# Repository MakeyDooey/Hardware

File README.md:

# Hardware
This includes all CAD files, PCB designs, schematics, datasheets, and designs. (includes enclosure and modularity components)

In it's current state I do not have a .gitignore for this repo. I will make one eventually and organize the repo more, but for now all KiCAD files are saved in the Schematic Folder as they are saved on my local computer

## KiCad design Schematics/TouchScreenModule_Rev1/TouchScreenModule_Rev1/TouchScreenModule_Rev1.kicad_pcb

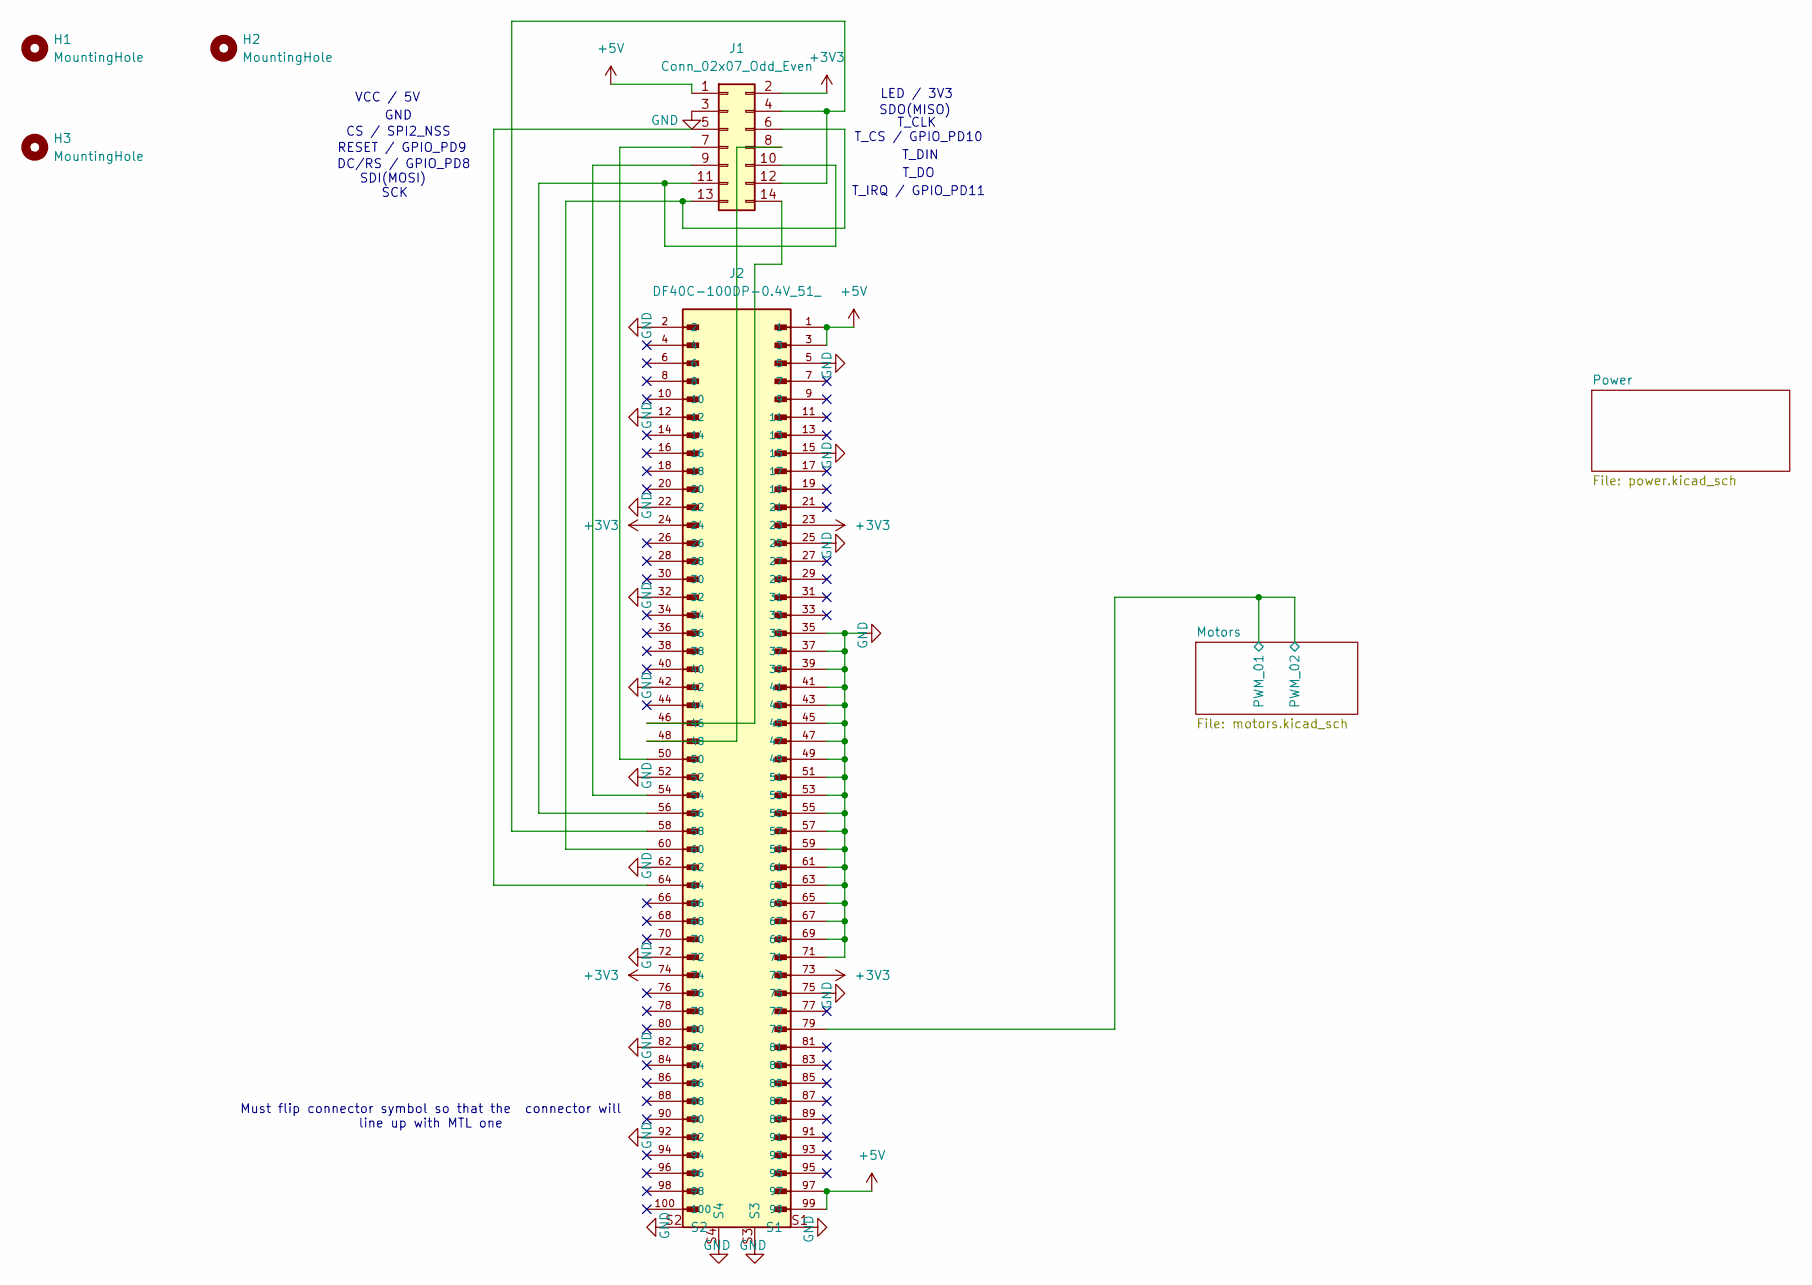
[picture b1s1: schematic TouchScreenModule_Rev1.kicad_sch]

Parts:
H1, H2, H3: MountingHole; MountingHole_3.2mm_M3_Pad_TopOnly
J1: Conn_02x07_Odd_Even; PinHeader_2x07_P2.54mm_Vertical
J2: DF40C-100DP-0.4V_51_; HIROSE_DF40C-100DP-0.4V_51_; PARTREV 8

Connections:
+3V3: J1.2, J2.23, J2.24, J2.73, J2.74
+5V: J1.1, J2.1, J2.3, J2.97, J2.99; also elsewhere on the board
/Motors/PWM_01: J2.79; also elsewhere on the board
GND: J1.3, J2.2, J2.5, J2.12, J2.15, J2.22, J2.25, J2.32, J2.35, J2.37, J2.39, J2.41, J2.42, J2.43, J2.45, J2.47, J2.49, J2.51, J2.52, J2.53, J2.55, J2.57, J2.59, J2.61, J2.62, J2.63, J2.65, J2.67, J2.69, J2.71, J2.72, J2.75, J2.82, J2.92, J2.S1, J2.S2, J2.S3, J2.S4; also elsewhere on the board
unnamed: J1.5, J2.64
unnamed: J1.7, J2.50
unnamed: J1.8, J2.48
unnamed: J1.9, J2.54
unnamed: J1.10, J1.11, J2.56
unnamed: J1.4, J1.12, J2.58
unnamed: J1.6, J1.13, J2.60
unnamed: J1.14, J2.46

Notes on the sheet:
T_CLK
CS / SPI2_NSS
GND
SCK
T_IRQ / GPIO_PD11
T_CS / GPIO_PD10
SDI(MOSI)
RESET / GPIO_PD9
T_DIN
T_DO
VCC / 5V
DC/RS / GPIO_PD8
SDO(MISO)
Must flip connector symbol so that the connector will line up with MTL one
LED / 3V3

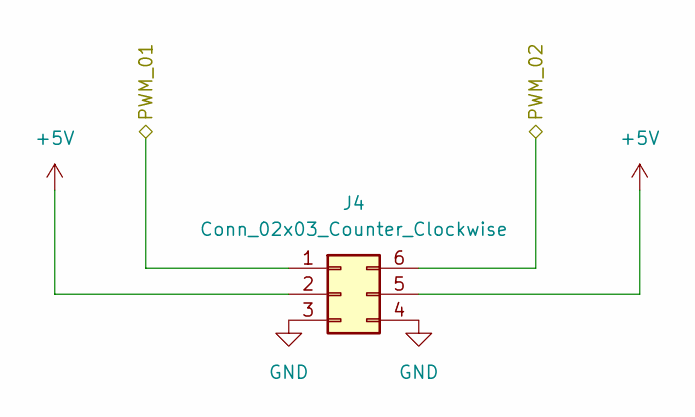
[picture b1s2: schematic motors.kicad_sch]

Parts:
J4: Conn_02x03_Counter_Clockwise; PinHeader_2x03_P2.54mm_Vertical

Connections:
+5V: J4.2, J4.5; also elsewhere on the board
/Motors/PWM_01: J4.1, J4.6; also elsewhere on the board
GND: J4.3, J4.4; also elsewhere on the board

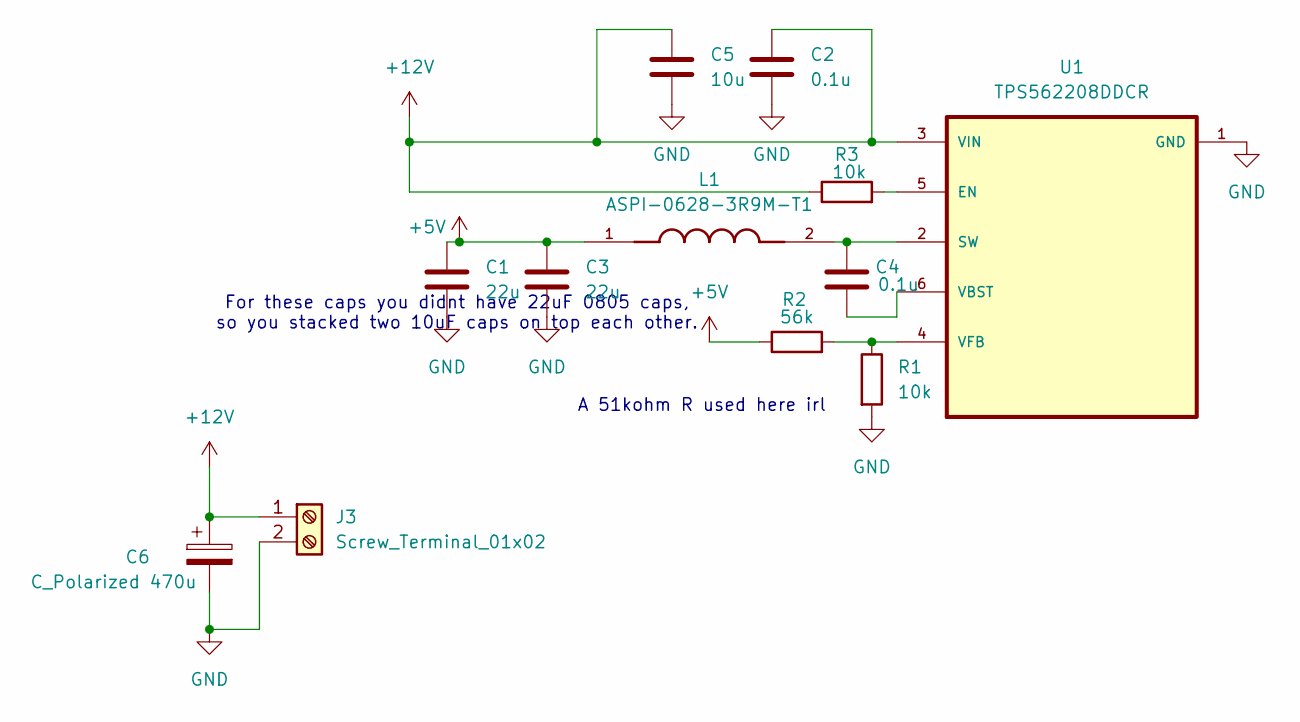
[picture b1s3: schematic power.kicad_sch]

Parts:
C1, C3: 22u; C_0805_2012Metric_Pad1.18x1.45mm_HandSolder
C2, C4: 0.1u; C_0805_2012Metric_Pad1.18x1.45mm_HandSolder
C5: 10u; C_0805_2012Metric_Pad1.18x1.45mm_HandSolder
C6: C_Polarized 470u; CP_Radial_D6.3mm_P2.50mm
J3: Screw_Terminal_01x02; TerminalBlock_Phoenix_MKDS-1,5-2-5.08_1x02_P5.08mm_Horizont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
L1: ASPI-0628-3R9M-T1; IND_ASPI-0628-3R9M-T1; PARTREV 6/30/2022
R1, R3: 10k; R_0805_2012Metric_Pad1.20x1.40mm_HandSolder
R2: 56k; R_0805_2012Metric_Pad1.20x1.40mm_HandSolder
U1: TPS562208DDCR

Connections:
+5V: C1.1, C3.1, L1.1, R2.1; also elsewhere on the board
+12V: C2.1, C5.1, C6.1, J3.1, R3.1, U1.3 (VIN)
GND: C1.2, C2.2, C3.2, C5.2, C6.2, J3.2, R1.2, U1.1 (GND); also elsewhere on the board
unnamed: R3.2, U1.5 (EN)
unnamed: C4.2, L1.2, U1.2 (SW)
unnamed: C4.1, U1.6 (VBST)
unnamed: R1.1, R2.2, U1.4 (VFB)

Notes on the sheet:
For these caps you didnt have 22uF 0805 caps, so you stacked two 10uF caps on top each other.
A 51kohm R used here irl

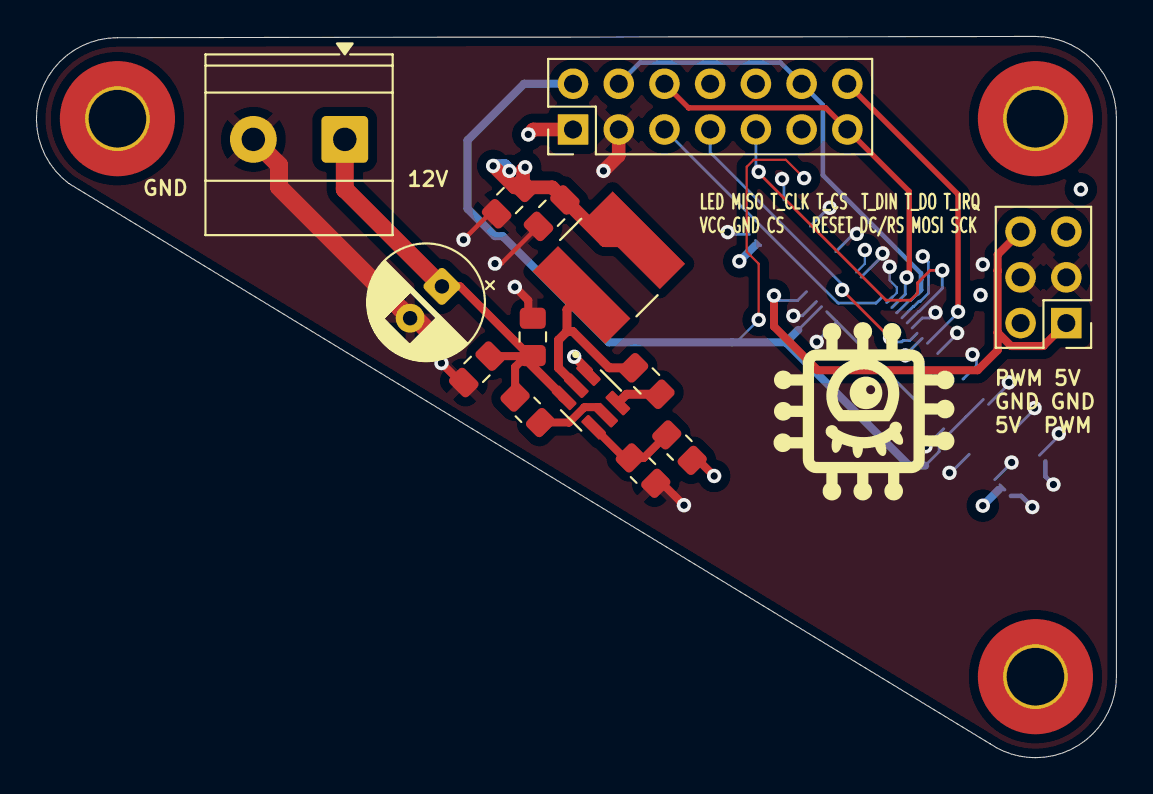
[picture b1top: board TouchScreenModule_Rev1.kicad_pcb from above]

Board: 4 copper layers, 60.0 x 40.1 mm, 18 parts (1 on the bottom side), 17 nets.

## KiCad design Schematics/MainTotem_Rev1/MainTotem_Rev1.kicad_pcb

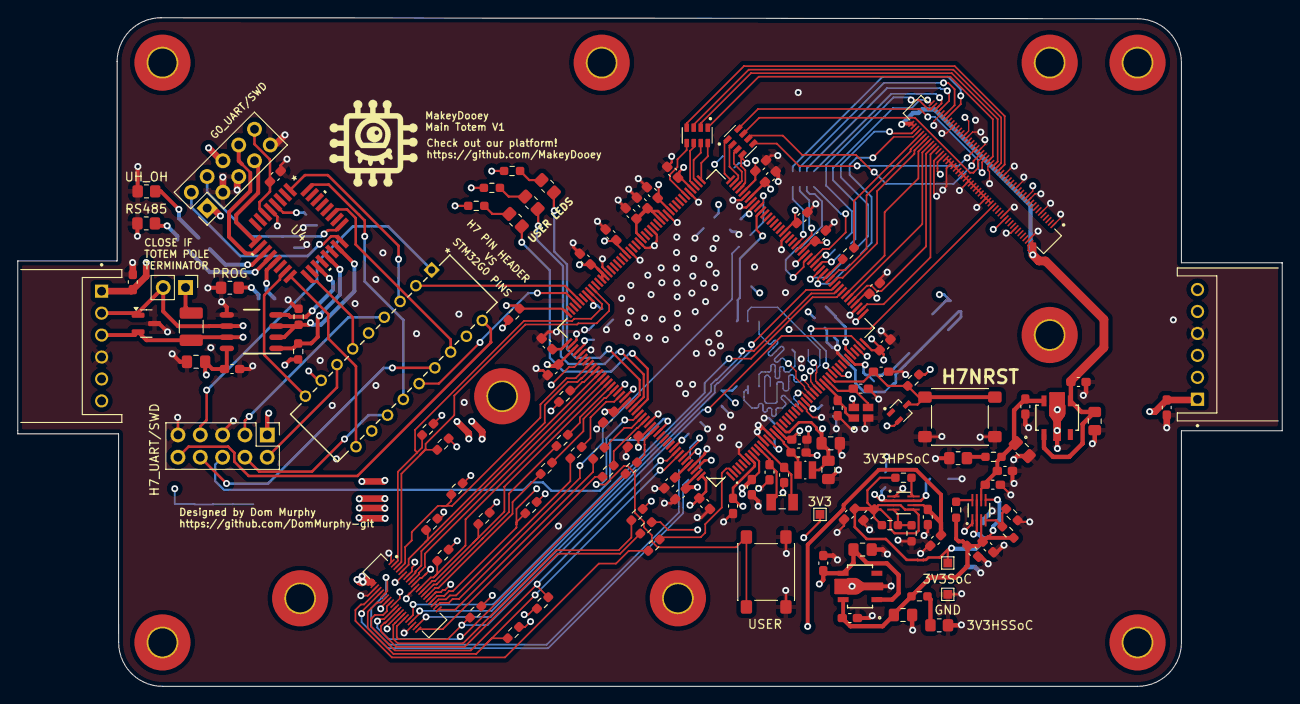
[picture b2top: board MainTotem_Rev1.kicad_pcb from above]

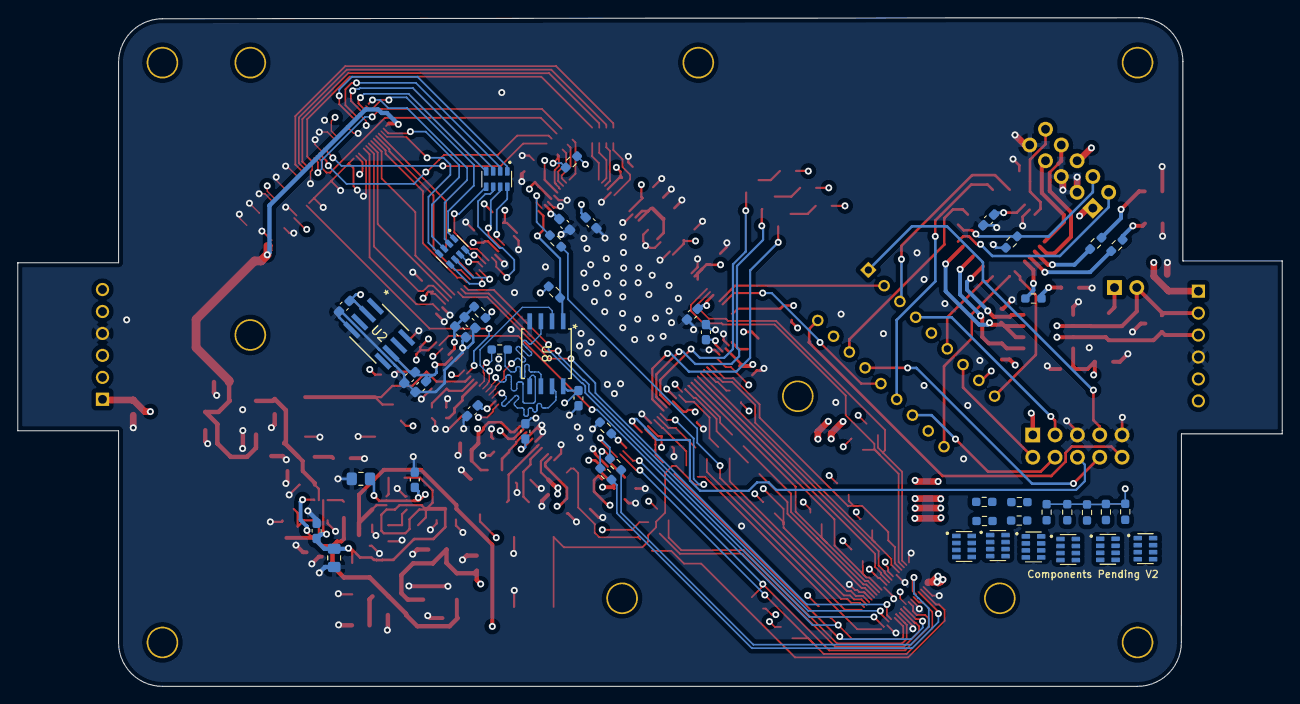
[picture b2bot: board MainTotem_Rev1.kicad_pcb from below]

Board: 4 copper layers, 143.9 x 76.1 mm, 181 parts (48 on the bottom side), 159 nets.

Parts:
3V3, 3V3SoC: TestPoint; TestPoint_Pad_1.0x1.0mm
3V3HPSoC: YELLOW; R_0805_2012Metric_Pad1.20x1.40mm_HandSolder
3V3HSSoC: GREEN; R_0805_2012Metric_Pad1.20x1.40mm_HandSolder
C1, C2, C3, C4, C5, C6, C7, C8, C9, C10, C11, C12, C13, C14, C15, C16, C19, C21, C22, C26, C27, C32, C34, C35, C38, C39, C47, C48, C49, C51, C52, C54, C63: 100n; C_0603_1608Metric_Pad1.08x0.95mm_HandSolder
C17, C41, C43, C72, C74: 4.7u; C_0603_1608Metric_Pad1.08x0.95mm_HandSolder
C18, C20: 1u; C_0603_1608Metric_Pad1.08x0.95mm_HandSolder
C23, C25, C42, C44, C45, C64, C73, C75, C76: 0.1u; C_0603_1608Metric_Pad1.08x0.95mm_HandSolder
C24, C33, C36, C37, C40: 10u; C_0805_2012Metric_Pad1.18x1.45mm_HandSolder
C28, C29, C30, C31: 2.2u ESR<100m; C_0603_1608Metric_Pad1.08x0.95mm_HandSolder
C46, C77: 22u; C_0805_2012Metric_Pad1.18x1.45mm_HandSolder
C55: 4.7u ESR<100m; C_0603_1608Metric_Pad1.08x0.95mm_HandSolder
C56: 220pF; C_0603_1608Metric_Pad1.08x0.95mm_HandSolder
C57, C58: 10u ESR<20m; C_0805_2012Metric_Pad1.18x1.45mm_HandSolder
C59, C60: 12p; C_0603_1608Metric_Pad1.08x0.95mm_HandSolder
C61, C62: 15p; C_0603_1608Metric_Pad1.08x0.95mm_HandSolder
D1: SM712_SOT23; SOT-23
D2: GREEN; R_0805_2012Metric_Pad1.20x1.40mm_HandSolder
D3: YELLOW; R_0805_2012Metric_Pad1.20x1.40mm_HandSolder
D4: BAT54SW_115
D6: RED; R_0805_2012Metric_Pad1.20x1.40mm_HandSolder
FB1: MFBW1V1608-601-R; R_0603_1608Metric_Pad0.98x0.95mm_HandSolder
GND: TestPoint; TestPoint_Pad_1.0x1.0mm
H1, H2, H3, H4, H5, H7, H8, H9, H10, H11: MountingHole; MountingHole_3.2mm_M3_Pad_TopOnly
H7RST1: SW_Push; SW_SPST_PTS645Sx43SMTR92
H7_UART/SWD: Conn_02x05_Odd_Even; PinHeader_2x05_P2.54mm_Vertical
J1, J2: S6B-XH-A; JST_S6B-XH-A
J3: Conn_02x05_Odd_Even; PinHeader_2x05_P2.54mm_Vertical
J5: DF40C-100DS-0.4V_51_; HIROSE_DF40C-100DS-0.4V_51_
J6: DF40C-40DS-0.4V_51_; HIROSE_DF40C-40DS-0.4V_51_
JP1: Jumper_2_Open; PinHeader_1x02_P2.54mm_Vertical
L1: VLS252012CX-2R2M-1; IND_VLS252012CX-2R2M-1
MainClock1: ABM10W-24.0000MHZ-8-D1X-T3; XTAL_ABM10W-24.0000MHZ-8-D1X-T3
PROG: GREEN; R_0805_2012Metric_Pad1.20x1.40mm_HandSolder
R1: 120; R_1210_3225Metric_Pad1.30x2.65mm_HandSolder
R2, R3, R4, R5, R6, R7, R16, R25, R26, R27, R28, R29, R31, R32, R48, R49, R52, R53: 10k; R_0603_1608Metric_Pad0.98x0.95mm_HandSolder
R8, R9, R10, R11, R12, R17, R18, R22: 1k; R_0603_1608Metric_Pad0.98x0.95mm_HandSolder
R13, R20: 56k; R_0603_1608Metric_Pad0.98x0.95mm_HandSolder
R14, R19: 110k; R_0603_1608Metric_Pad0.98x0.95mm_HandSolder
R15, R21: 100k; R_0603_1608Metric_Pad0.98x0.95mm_HandSolder
R23, R24, R44, R50, R51: 4.7k; R_0603_1608Metric_Pad0.98x0.95mm_HandSolder
R30, R33, R34, R35, R36, R37, R38, R39, R40, R41, R42, R43, R45, R46, R47, R54, R55, R56, R57: 33; R_0603_1608Metric_Pad0.98x0.95mm_HandSolder
RN1, RN2, RN3, RN4, RN5, RN6, RN7, RN8, RN9, RN10: CAY16-330J4LF; 33ohmresarray
RS485: YELLOW; R_0805_2012Metric_Pad1.20x1.40mm_HandSolder
RTC1: ABS07-32.768KHZ-9-T; XTAL_ABS07-32.768KHZ-9-T
SW1: 3-1825010-8; SW6_3-1825010-8_TEC
U1: STM32H757IIT6; LQFP-176
U2: ADR4525BRZ-R7; R_8_ADI-M
U3: THVD1450D; D0008A_M
U4: STM32G071KBT6; LQFP-32-M
U5, U6: AP7361C-33Y5-13; SOT89-5_DIO-M
U7, U11: PTPS2117DRLR; SOT-5X3-8_DRL_TEX-M
U8: W25Q128JVSIQ TR; SOIC_208MIL_WIN-M
UH_OH: RED; R_0805_2012Metric_Pad1.20x1.40mm_HandSolder
USER: SW_Push; SW_SPST_PTS645Sx43SMTR92

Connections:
3V3MODULES: 3V3SoC.1, C45.1, C46.1, C72.1, C73.1, R19.1, R21.1, U7.2 (VOUT), U7.7 (VOUT), U11.3 (VIN1), U11.5 (MODE)
3V3PROGRAMMER: C23.1, C64.1, C74.1, C75.1, J1.1, J2.1, U11.6 (VIN2)
5VHPSoC: C33.1, C34.1, J5.2, J5.4, J5.98, J5.100, U5.1 (EN), U5.4 (IN)
5VHSSoC: C37.1, C38.1, J6.2, J6.4, U6.1 (EN), U6.4 (IN)
+3V3: 3V3.1, C1.1, C2.1, C3.1, C4.1, C5.1, C6.1, C7.1, C8.1, C9.1, C10.1, C11.1, C12.1, C13.1, C14.1, C15.1, C16.1, C17.1, C22.1, C24.1, C25.1, C32.1, C51.1, C54.1, C55.1, C63.1, C76.1, C77.1, FB1.2, H7_UART/SWD.1, J3.1, J3.6, J5.23, J5.24, J5.73, J5.74, J6.19, J6.20, R2.1, R5.1, R6.1, R16.2, R17.1, R18.1, R22.1, R23.1, R24.1, R25.1, R26.1, R27.1, R28.1, R29.1, R31.1, R32.1, R44.1, R48.1, R49.1, R50.1, R51.1, R52.1, R53.1, U1.7 (VDD), U1.8 (VBAT), U1.13 (VDD), U1.16 (VDDSMPS), U1.25 (VDD), U1.44 (VDD), U1.48 (VDD), U1.65 (VDD), U1.71 (VDD), U1.84 (VDD), U1.92 (VDD), U1.99 (VDD), U1.113 (VDD), U1.120 (VDD50USB), U1.121 (VDD33USB), U1.126 (VDD), U1.136 (VDD), U1.152 (VDD), U1.160 (VDD), U1.174 (PDR_ON), U1.176 (VDD), U2.2 (VIN), U3.8 (VCC), U4.4 (VDD), U8.8 (VCC), U11.2 (VOUT), U11.7 (VOUT)
/MCU2/40P_CONN/FDCAN_RX: J6.15, U1.143 (PD0)
/MCU2/40P_CONN/FDCAN_TX: J6.17, U1.144 (PD1)
/MCU2/40P_CONN/GPIO_PD7: R35.1, U1.150 (PD7)
/MCU2/40P_CONN/GPIO_PE0: R42.1, U1.170 (PE0)
/MCU2/40P_CONN/GPIO_PE1: R43.1, U1.171 (PE1)
/MCU2/40P_CONN/GPIO_PE3: R45.1, U1.2 (PE3)
/MCU2/40P_CONN/I2C1_SCL: J6.18, R23.2, U1.168 (PB8)
/MCU2/40P_CONN/I2C1_SDA: J6.14, R24.2, U1.169 (PB9)
/MCU2/40P_CONN/SDMMC1_CK: R30.1, U1.142 (PC12)
/MCU2/40P_CONN/SDMMC1_CMP: J6.23, R25.2, U1.145 (PD2)
/MCU2/40P_CONN/SDMMC1_D0: J6.5, R28.2, U1.124 (PC8)
/MCU2/40P_CONN/SDMMC1_D1: J6.3, R29.2, U1.125 (PC9)
/MCU2/40P_CONN/SDMMC1_D2: J6.7, R27.2, U1.140 (PC10)
/MCU2/40P_CONN/SDMMC1_D3: J6.9, R26.2, U1.141 (PC11)
/MCU2/40P_CONN/USART2_CTS: J6.25, R32.2, U1.146 (PD3)
/MCU2/40P_CONN/USART2_RTS: R33.1, U1.147 (PD4)
/MCU2/40P_CONN/USART2_RX: J6.33, R31.2, U1.149 (PD6)
/MCU2/40P_CONN/USART2_TX: R34.1, U1.148 (PD5)
/MCU2/100P_CONN/ADC_PA3: J5.80, U1.46 (PA3)
/MCU2/100P_CONN/ADC_PA6: J5.86, U1.51 (PA6)
/MCU2/100P_CONN/ADC_PB0: J5.88, U1.55 (PB0)
/MCU2/100P_CONN/ADC_PB1: J5.90, U1.56 (PB1)
/MCU2/100P_CONN/ADC_PC0: J5.34, U1.34 (PC0)
/MCU2/100P_CONN/DAC_ADC_PA4: J5.82, U1.49 (PA4)
/MCU2/100P_CONN/DAC_ADC_PA5: J5.84, U1.50 (PA5)
/MCU2/100P_CONN/GPIO_PB2: R54.1, U1.57 (PB2)
/MCU2/100P_CONN/GPIO_PE7: RN7.8, U1.67 (PE7)
/MCU2/100P_CONN/GPIO_PG0: RN7.6, U1.63 (PG0)
/MCU2/100P_CONN/GPIO_PG1: RN7.7, U1.66 (PG1)
/MCU2/QSPIMEM/QUADSPI_BK1_CLK: R57.1, U1.30 (PF10)
/MCU2/QSPIMEM/QUADSPI_BK1_IO0: U1.28 (PF8), U8.5 (DI(IO0))
/MCU2/QSPIMEM/QUADSPI_BK1_IO1: U1.29 (PF9), U8.2 (DO(IO1))
/MCU2/QSPIMEM/QUADSPI_BK1_IO2: U1.27 (PF7), U8.3 (/WP(IO2))
/MCU2/QSPIMEM/QUADSPI_BK1_IO3: U1.26 (PF6), U8.7 (/HOLD_/RESET)
BUSH7BOOT0: SW1.16, U4.27 (PB3)
BUSH7NRST: SW1.6, U4.17 (PB2)
BUSH7SWCLK: SW1.10, U4.16 (PB1)
BUSH7SWDIO: SW1.9, U4.15 (PB0)
BUSH7UARTRX: SW1.13, U4.32 (PB8)
BUSHH7UARTTX: SW1.3, U4.1 (PB9)
G0UARTRX: J3.8, U4.10 (PA3)
G0UARTTX: J3.7, U4.9 (PA2)
GND: 3V3HPSoC.1 (K), 3V3HSSoC.1 (K), C1.2, C2.2, C3.2, C4.2, C5.2, C6.2, C7.2, C8.2, C9.2, C10.2, C11.2, C12.2, C13.2, C14.2, C15.2, C16.2, C17.2, C18.2, C19.2, C20.2, C21.2, C22.2, C23.2, C24.2, C25.2, C26.2, C27.2, C28.2, C29.2, C30.2, C31.2, C32.2, C33.2, C34.2, C35.2, C36.2, C37.2, C38.2, C39.2, C40.2, C41.2, C42.2, C43.2, C44.2, C45.2, C46.2, C47.2, C48.2, C49.2, C51.2, C52.2, C54.2, C55.2, C56.2, C57.2, C58.2, C59.2, C60.2, C61.2, C62.2, C63.2, C64.2, C72.2, C73.2, C74.2, C75.2, C76.2, C77.2, D1.3 (common), GND.1, H7RST1.2, H7_UART/SWD.5, H7_UART/SWD.9, J1.4, J2.4, J3.3, J3.5, J3.9, J5.1, J5.6, J5.11, J5.16, J5.21, J5.26, J5.31, J5.36, J5.38, J5.40, J5.41, J5.42, J5.44, J5.46, J5.48, J5.50, J5.51, J5.52, J5.54, J5.56, J5.58, J5.60, J5.61, J5.62, J5.64, J5.66, J5.68, J5.70, J5.71, J5.72, J5.76, J5.81, J5.91, J6.1, J6.6, J6.11, J6.16, J6.21, J6.26, J6.31, J6.36, MainClock1.2 (GND), MainClock1.4 (GND__1), PROG.1 (K), R3.2, R4.2, R7.2, R13.2, R20.2, RS485.1 (K), U1.6 (VSS), U1.12 (VSS), U1.14 (VSSSMPS), U1.24 (VSS), U1.38 (VSSA), U1.45 (VSS), U1.47 (VSS), U1.64 (VSS), U1.70 (VSS), U1.81 (VSS), U1.83 (VSS), U1.93 (VSS), U1.100 (VSS), U1.105 (VSSDSI), U1.109 (VSSDSI), U1.112 (VSS), U1.119 (VSS), U1.134 (VSS), U1.137 (VSS), U1.151 (VSS), U1.159 (VSS), U1.173 (VSS), U2.4 (GND), U3.5 (GND), U4.5 (VSS), U5.2 (GND), U6.2 (GND), U7.1 (GND), U8.4 (GND), U11.1 (GND), UH_OH.1 (K), USER.2
GPIO_PG15: R41.1, U1.161 (PG15)
H7BOOT0: R4.1, SW1.17, U1.167 (BOOT0)
H7NRST: C26.1, D4.3, H7RST1.1, R5.2, U1.33 (NRST)
H7SWCLK: SW1.11, U1.138 (PA14)
H7SWDIO: R6.2, SW1.8, U1.132 (PA13)
H7SWO: H7_UART/SWD.6, U1.162 (PB3)
H7UARTRX: SW1.14, U1.129 (PA10)
H7UARTTX: SW1.2, U1.128 (PA9)
unnamed: 3V3HPSoC.2 (A), R11.2
unnamed: 3V3HSSoC.2 (A), R12.2
unnamed: C28.1, U1.172 (VCAP)
unnamed: C29.1, U1.133 (VCAP)
unnamed: C30.1, U1.80 (VCAP)
unnamed: D1.1 (A1), J1.2, J2.2, JP1.2 (B), U3.6 (A)
unnamed: D1.2 (A2), J1.3, J2.3, R1.2, U3.7 (B)
unnamed: D2.2 (A), R18.2
unnamed: D2.1 (K), U1.154 (PG10)
unnamed: D3.2 (A), R22.2
unnamed: D3.1 (K), U1.155 (PG11)
unnamed: D4.2, SW1.5
unnamed: D6.2 (A), R17.2
unnamed: D6.1 (K), U1.153 (PG9)
unnamed: H7_UART/SWD.2, SW1.7
unnamed: H7_UART/SWD.3, SW1.4
unnamed: H7_UART/SWD.4, SW1.12
unnamed: H7_UART/SWD.7, SW1.1
unnamed: H7_UART/SWD.8, SW1.15
unnamed: H7_UART/SWD.10, SW1.18
unnamed: J3.2, U4.24 (PA13)
unnamed: J3.4, R7.1, U4.25 (PA14-BOOT0)
unnamed: C27.1, J3.10, U4.6 (PF2-NRST)
unnamed: J5.45, RN1.4
unnamed: J5.47, RN1.3
unnamed: J5.49, RN1.2
unnamed: J5.53, RN1.1
unnamed: J5.55, RN4.8
unnamed: J5.57, RN4.7
unnamed: J5.59, RN4.6
unnamed: J5.63, RN4.5
unnamed: J5.87, RN7.1
unnamed: J5.89, RN7.2
unnamed: J5.92, R54.2
unnamed: J5.93, RN7.3
unnamed: J5.94, RN8.4
unnamed: J5.95, RN7.4
unnamed: J5.96, RN8.3
unnamed: J5.97, RN8.1
unnamed: J5.99, RN8.2
unnamed: J6.8, R45.2
unnamed: J6.10, R43.2
unnamed: J6.12, R42.2
unnamed: J6.13, R30.2
unnamed: J6.22, R41.2
unnamed: J6.24, R40.2
unnamed: J6.27, R33.2
unnamed: J6.28, R38.2
unnamed: J6.29, R34.2
unnamed: J6.35, R35.2
unnamed: J6.37, R39.2
unnamed: J6.39, R36.2
unnamed: J6.40, R37.2
unnamed: JP1.1 (A), R1.1
unnamed: PROG.2 (A), R10.2
unnamed: R9.2, RS485.2 (A)
unnamed: U1.156 (PG12), USER.1
unnamed: C31.1, C52.1, U1.101 (VCAPDSI), U1.102 (VDD12DSI), U1.108 (VDD12DSI)
unnamed: C18.1, C19.1, FB1.1, U1.40 (VDDA)
unnamed: C47.1, C48.1, C49.1, C57.1, C58.1, L1.1, U1.17 (VFBSMPS), U1.82 (VDDLDO), U1.135 (VDDLDO), U1.175 (VDDLDO)
unnamed: C56.1, L1.2, U1.15 (VLXSMPS)
unnamed: C20.1, C21.1, U1.39 (VREF+), U2.6 (VOUT)
unnamed: U3.4 (D), U4.19 (PA9)
unnamed: R3.1, U3.2 (RE_N), U3.3 (DE), U4.23 (PA12[PA10])
unnamed: R2.2, U3.1 (R), U4.21 (PA10)
unnamed: R8.1, U4.11 (PA4)
unnamed: R9.1, U4.12 (PA5)
unnamed: R10.1, U4.13 (PA6)
unnamed: C35.1, C36.1, C43.1, C44.1, R11.1, U5.5 (OUT), U7.6 (VIN2)
unnamed: C39.1, C40.1, C41.1, C42.1, R12.1, R14.1, R15.1, U6.5 (OUT), U7.3 (VIN1), U7.5 (MODE)
unnamed: R13.1, R14.2, U7.4 (PR1)
unnamed: R15.2, U7.8 (ST)
unnamed: R57.2, U8.6 (CLK)
unnamed: R19.2, R20.1, U11.4 (PR1)
unnamed: R21.2, U11.8 (ST)
unnamed: R8.2, UH_OH.2 (A)
OSC32_IN: C62.1, RTC1.1, U1.10 (PC14-OSC32_IN)
OSC32_OUT: C61.1, RTC1.2, U1.11 (PC15-OSC32_OUT)
OSC_IN: C60.1, MainClock1.1, U1.31 (PH0-OSC_IN)
OSC_OUT: C59.1, MainClock1.3, U1.32 (PH1-OSC_OUT)
PA1: R38.1, U1.42 (PA1)
PA2: J6.30, R44.2, U1.43 (PA2)
PA7: J6.32, U1.52 (PA7)
PB10: R16.1, U1.78 (PB10), U8.1 (/CS)
PB11: R39.1, U1.79 (PB11)
PC1: R40.1, U1.35 (PC1)
PC4: J6.34, U1.53 (PC4)
PC5: J6.38, U1.54 (PC5)
PD8: RN1.8, U1.89 (PD8)
PD9: RN1.7, U1.90 (PD9)
PD10: RN1.6, U1.91 (PD10)
PD11: RN1.5, U1.94 (PD11)
PF11: RN8.5, U1.58 (PF11)
PF12: RN8.6, U1.59 (PF12)
PF13: RN8.7, U1.60 (PF13)
PF14: RN8.8, U1.61 (PF14)
PF15: RN7.5, U1.62 (PF15)
PG13: R36.1, U1.157 (PG13)
PG14: R37.1, U1.158 (PG14)
SPI2_MISO: RN4.2, U1.87 (PB14)
SPI2_MOSI: RN4.1, U1.88 (PB15)
SPI2_NSS: R53.2, RN4.4, U1.85 (PB12)
SPI2_SCK: RN4.3, U1.86 (PB13)

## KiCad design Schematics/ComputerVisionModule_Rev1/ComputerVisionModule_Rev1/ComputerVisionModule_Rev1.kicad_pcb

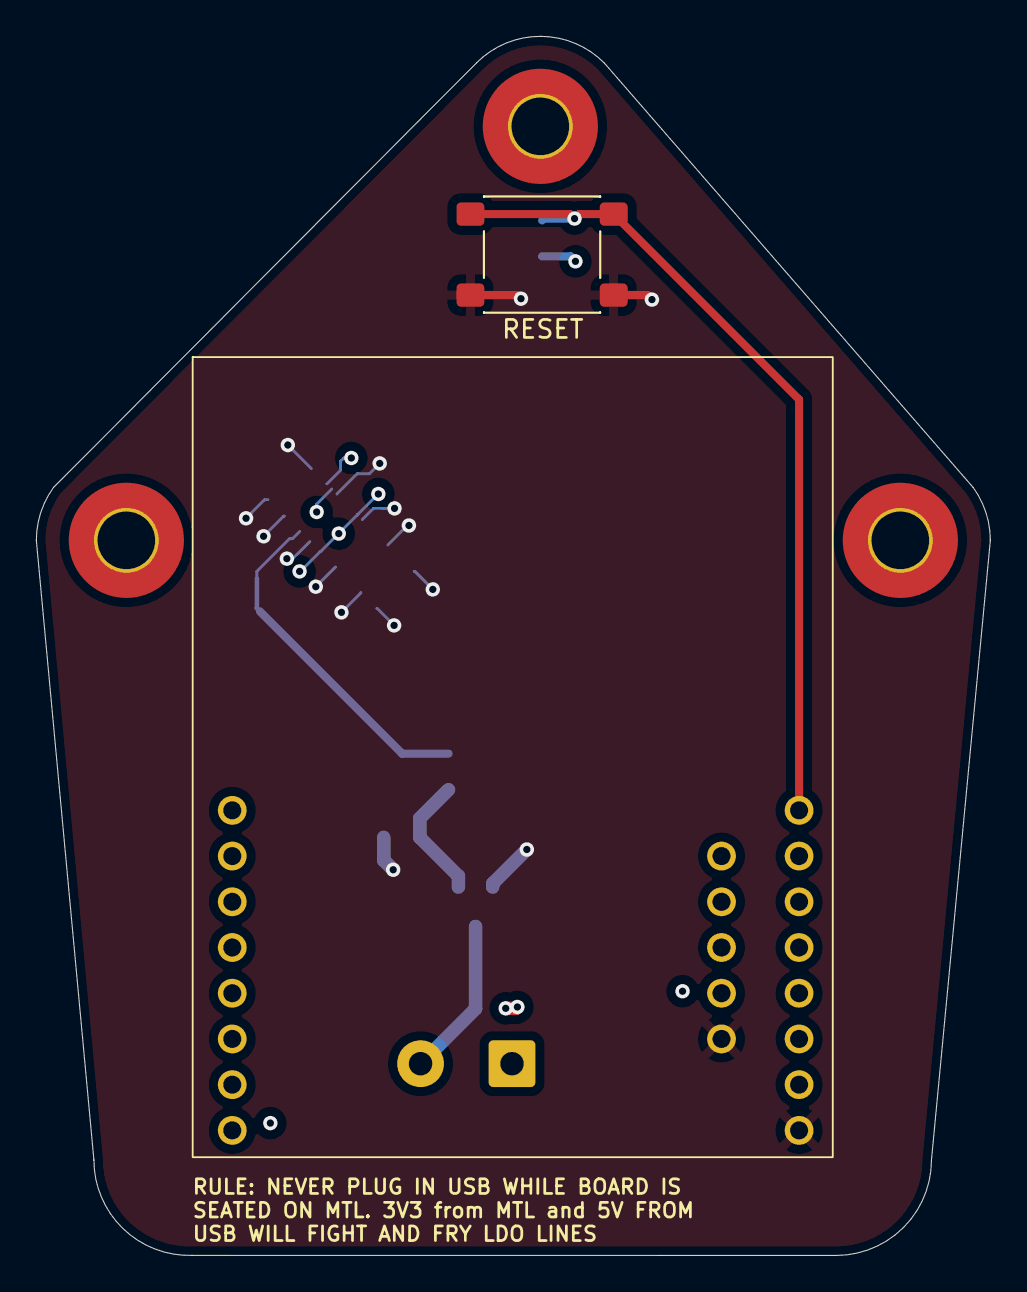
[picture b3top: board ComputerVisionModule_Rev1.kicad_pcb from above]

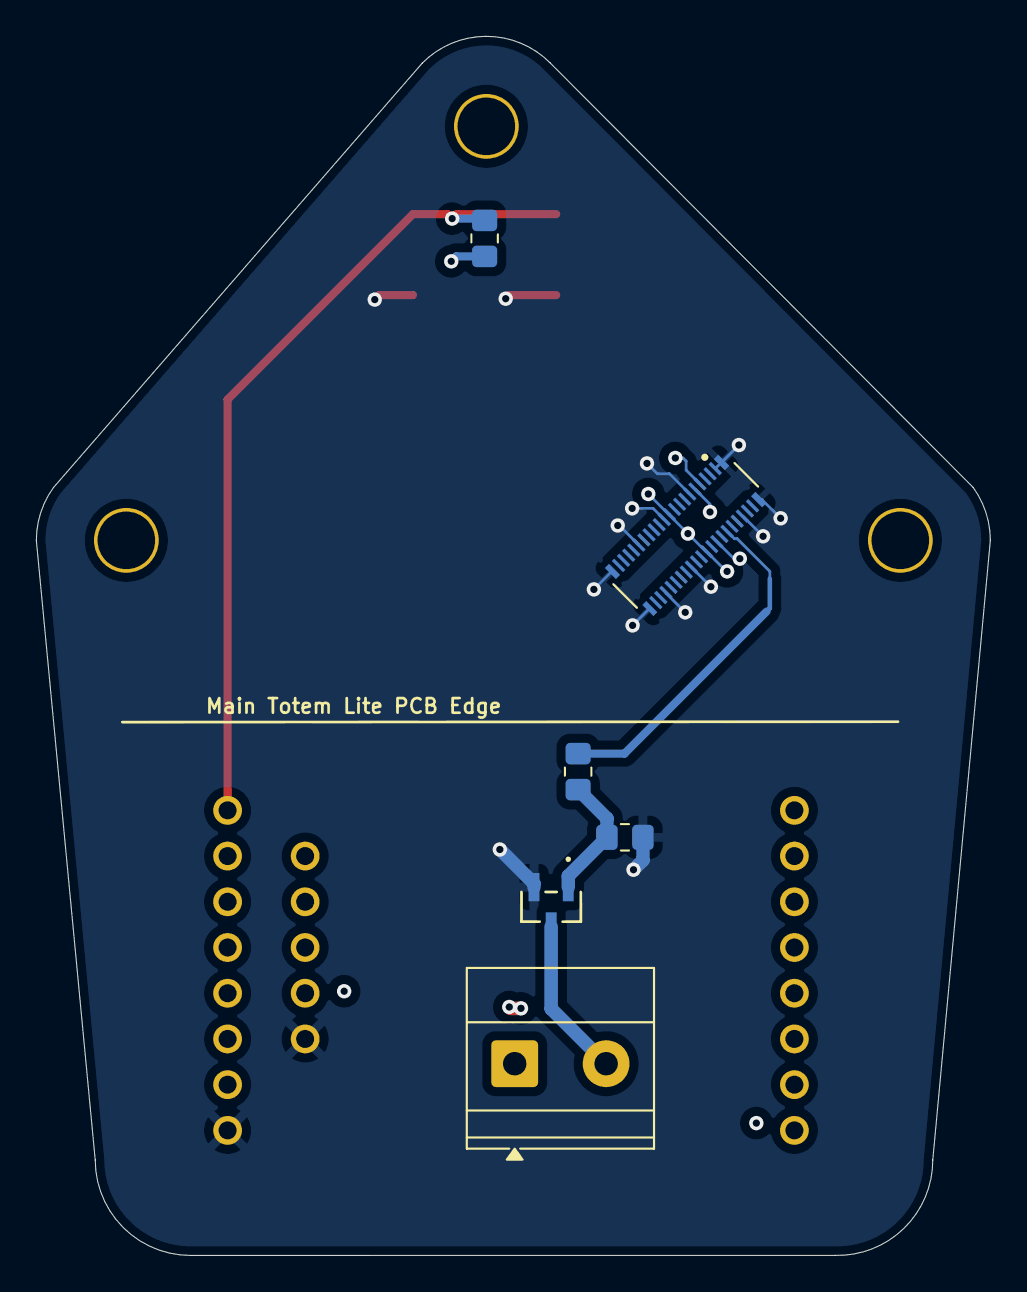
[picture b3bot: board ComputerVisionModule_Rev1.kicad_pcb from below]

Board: 4 copper layers, 53.0 x 67.7 mm, 11 parts (6 on the bottom side), 8 nets.

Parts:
H1, H2, H3: MountingHole; MountingHole_3.2mm_M3_Pad_TopOnly
J1: DF40C-40DP-0.4V_51_; HRS_DF40C-40DP-0.4V_51_
J2: Screw_Terminal_01x02; TerminalBlock_Phoenix_MKDS-1,5-2-5.08_1x02_P5.08mm_Horizont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
R1, R3: 10k; R_0805_2012Metric_Pad1.20x1.40mm_HandSolder
R2: 100; R_0805_2012Metric_Pad1.20x1.40mm_HandSolder
SW1: SW_Push; SW_SPST_PTS645Sx43SMTR92
U1: OPENMV4_H7
U2: BSS138; SOT-23_3L_ONS-M

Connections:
+3V3: J1.19, J1.20, J2.1, R1.1, U1.1 (3V3), U1.7 (3V3)
GND: J1.1, J1.6, J1.11, J1.16, J1.21, J1.26, J1.31, J1.36, J1.S1 (SHIELD), J1.S2 (SHIELD__1), J1.S3 (SHIELD__2), J1.S4 (SHIELD__3), R3.2, SW1.2, U1.3 (GND), U1.5 (GND), U2.2 (S)
unnamed: J1.12, R2.1
unnamed: J2.2, U2.3 (D)
unnamed: R1.2, SW1.1, U1.6 (RST)
unnamed: J1.7, U1.4 (RX)
unnamed: J1.9, U1.2 (TX)
unnamed: R2.2, R3.1, U2.1 (G)

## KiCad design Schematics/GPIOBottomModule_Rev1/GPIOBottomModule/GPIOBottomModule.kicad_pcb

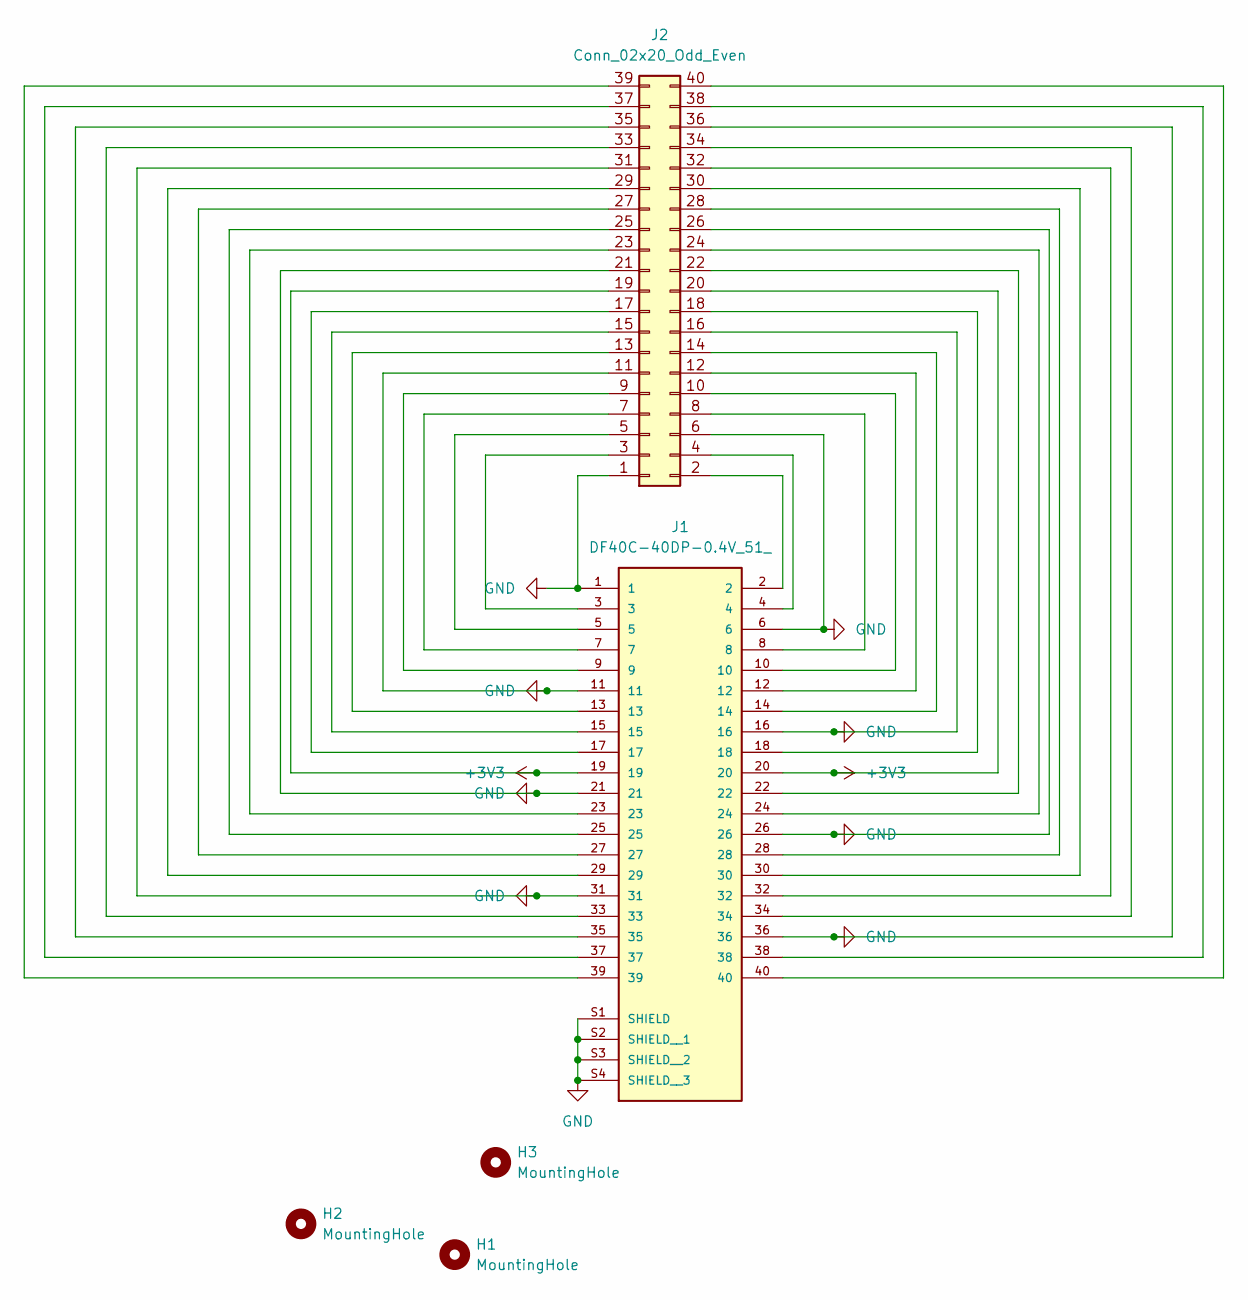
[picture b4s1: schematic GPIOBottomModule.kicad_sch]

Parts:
H1, H2, H3: MountingHole; MountingHole_3.2mm_M3_Pad_TopOnly
J1: DF40C-40DP-0.4V_51_; HRS_DF40C-40DP-0.4V_51_
J2: Conn_02x20_Odd_Even; PinHeader_2x20_P2.54mm_Vertical

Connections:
+3V3: J1.19, J1.20, J2.19, J2.20
GND: J1.1, J1.6, J1.11, J1.16, J1.21, J1.26, J1.31, J1.36, J1.S1 (SHIELD), J1.S2 (SHIELD__1), J1.S3 (SHIELD__2), J1.S4 (SHIELD__3), J2.1, J2.6, J2.11, J2.16, J2.21, J2.26, J2.31, J2.36
unnamed: J1.2, J2.2
unnamed: J1.3, J2.3
unnamed: J1.4, J2.4
unnamed: J1.5, J2.5
unnamed: J1.7, J2.7
unnamed: J1.8, J2.8
unnamed: J1.9, J2.9
unnamed: J1.10, J2.10
unnamed: J1.12, J2.12
unnamed: J1.13, J2.13
unnamed: J1.14, J2.14
unnamed: J1.15, J2.15
unnamed: J1.17, J2.17
unnamed: J1.18, J2.18
unnamed: J1.22, J2.22
unnamed: J1.23, J2.23
unnamed: J1.24, J2.24
unnamed: J1.25, J2.25
unnamed: J1.27, J2.27
unnamed: J1.28, J2.28
unnamed: J1.29, J2.29
unnamed: J1.30, J2.30
unnamed: J1.32, J2.32
unnamed: J1.33, J2.33
unnamed: J1.34, J2.34
unnamed: J1.35, J2.35
unnamed: J1.37, J2.37
unnamed: J1.38, J2.38
unnamed: J1.39, J2.39
unnamed: J1.40, J2.40

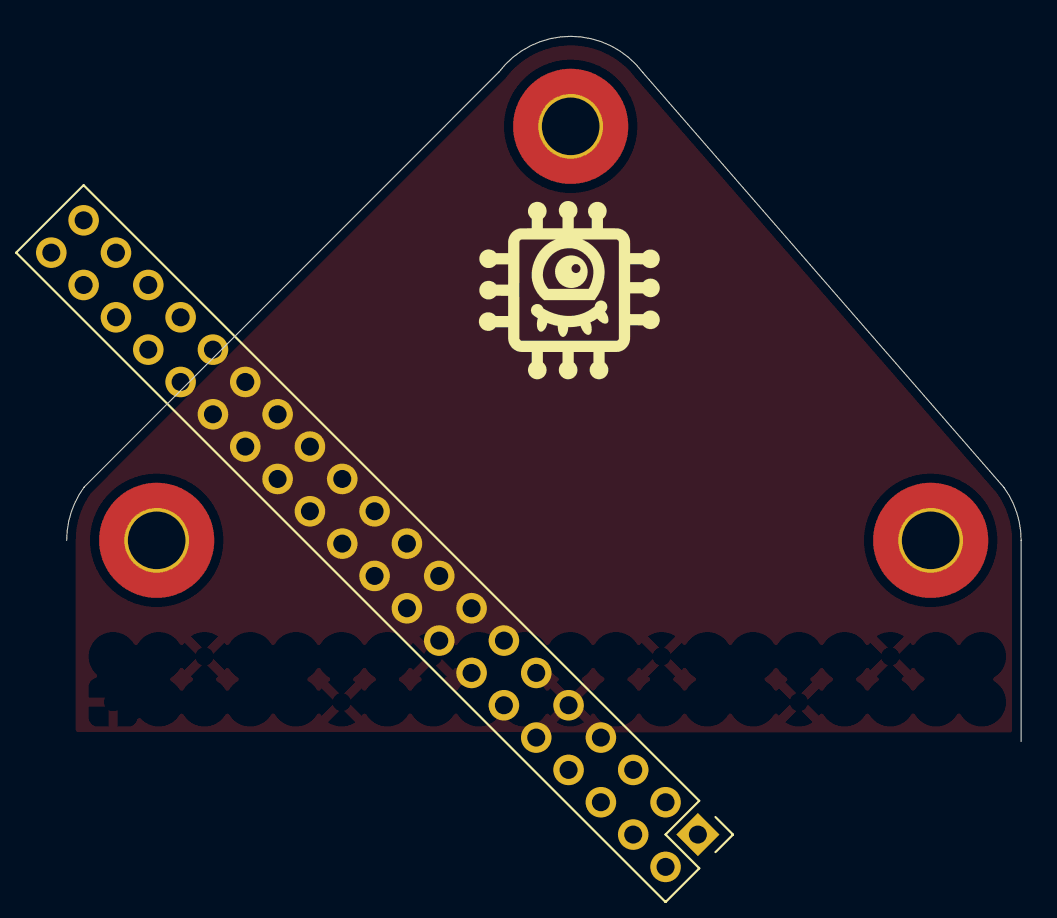
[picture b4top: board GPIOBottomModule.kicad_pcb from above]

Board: 4 copper layers, 53.0 x 39.2 mm, 5 parts (1 on the bottom side), 32 nets.
